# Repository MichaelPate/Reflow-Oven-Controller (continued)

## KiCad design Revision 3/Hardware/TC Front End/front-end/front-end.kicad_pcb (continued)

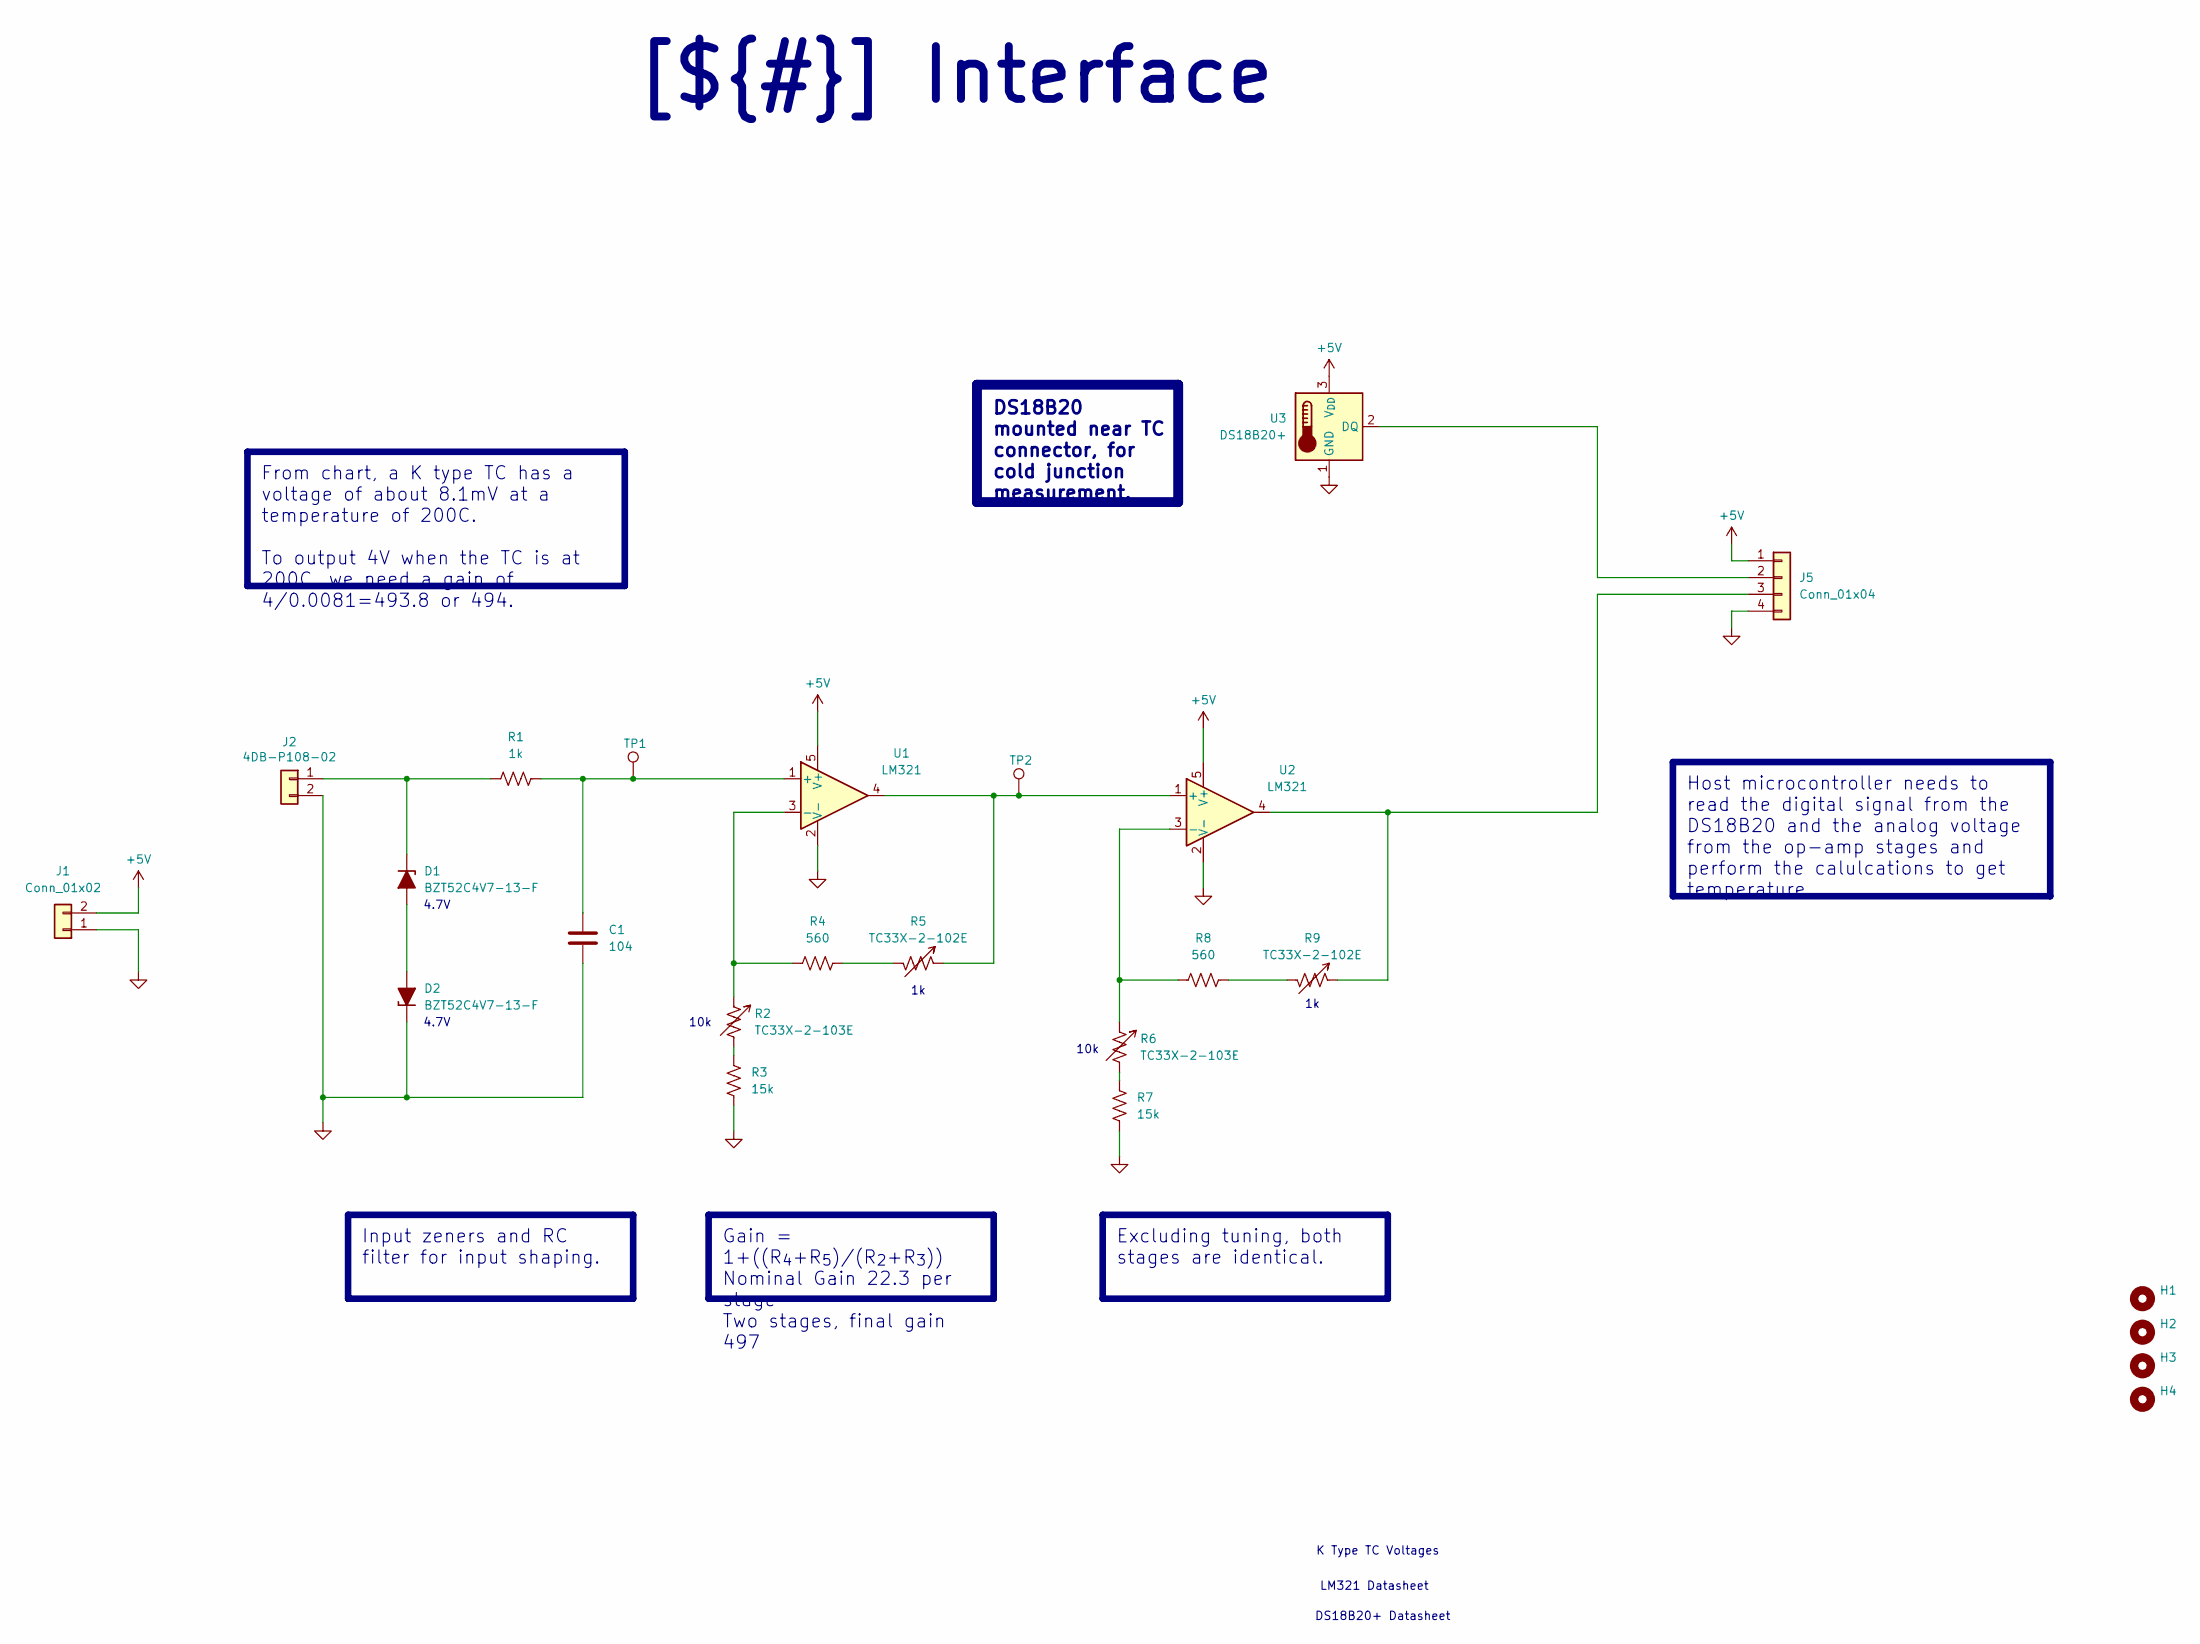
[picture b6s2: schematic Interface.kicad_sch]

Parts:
C1: 104; C_0603_1608Metric_Pad1.08x0.95mm_HandSolder
D1, D2: BZT52C4V7-13-F; D_SOD-123
H1, H2, H3, H4: MountingHole; MountingHole_3.2mm_M3
J1: Conn_01x02; TerminalBlock_Phoenix_MKDS-1,5-2_1x02_P5.00mm_Horizontal
J2: 4DB-P108-02; CONN_4DB-P108-02_TEC
J5: Conn_01x04; PinHeader_1x04_P2.54mm_Vertical
R1: 1k; R_0603_1608Metric_Pad0.98x0.95mm_HandSolder
R2, R6: TC33X-2-103E; Potentiometer_Bourns_TC33X_Vertical
R3, R7: 15k; R_0603_1608Metric_Pad0.98x0.95mm_HandSolder
R4, R8: 560; R_0603_1608Metric_Pad0.98x0.95mm_HandSolder
R5, R9: TC33X-2-102E; Potentiometer_Bourns_TC33X_Vertical
TP1, TP2: TestPoint; TestPoint_THTPad_D2.0mm_Drill1.0mm
U1, U2: LM321; SOT-23-5
U3: DS18B20+; TO-92_Inline

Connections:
+5V: J1.2, J5.1, U1.5 (V+), U2.5 (V+), U3.3 (V_{DD})
GND: C1.2, D2.1 (K), J1.1, J2.2, J5.4, R3.2, R7.2, U1.2 (V-), U2.2 (V-), U3.1 (GND)
unnamed: D1.2 (A), D2.2 (A)
unnamed: D1.1 (K), J2.1, R1.1
unnamed: J5.2, U3.2 (DQ)
unnamed: J5.3, R9.1, U2.4
unnamed: R2.2, R3.1
unnamed: R4.2, R5.2
unnamed: R6.2, R7.1
unnamed: R8.2, R9.2
unnamed: C1.1, R1.2, TP1.1, U1.1 (+)
unnamed: R2.1, R4.1, U1.3 (-)
unnamed: R5.1, TP2.1, U1.4, U2.1 (+)
unnamed: R6.1, R8.1, U2.3 (-)

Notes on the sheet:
4.7V
K Type TC Voltages
10k
LM321 Datasheet
DS18B20+ Datasheet
DS18B20 mounted near TC connector, for cold junction measurement.
Gain = 1+((R_{4}+R_{5})/(R_{2}+R_{3})) Nominal Gain 22.3 per stage Two stages, final gain 497
Input zeners and RC filter for input shaping.
Excluding tuning, both stages are identical.
[${#}] ${TITLE}
Host microcontroller needs to read the digital signal from the DS18B20 and the analog voltage from the op-amp stages and perform the calulcations to get temperature.
From chart, a K type TC has a voltage of about 8.1mV at a temperature of 200C. To output 4V when the TC is at 200C, we need a gain of 4/0.0081=493.8 or 494.

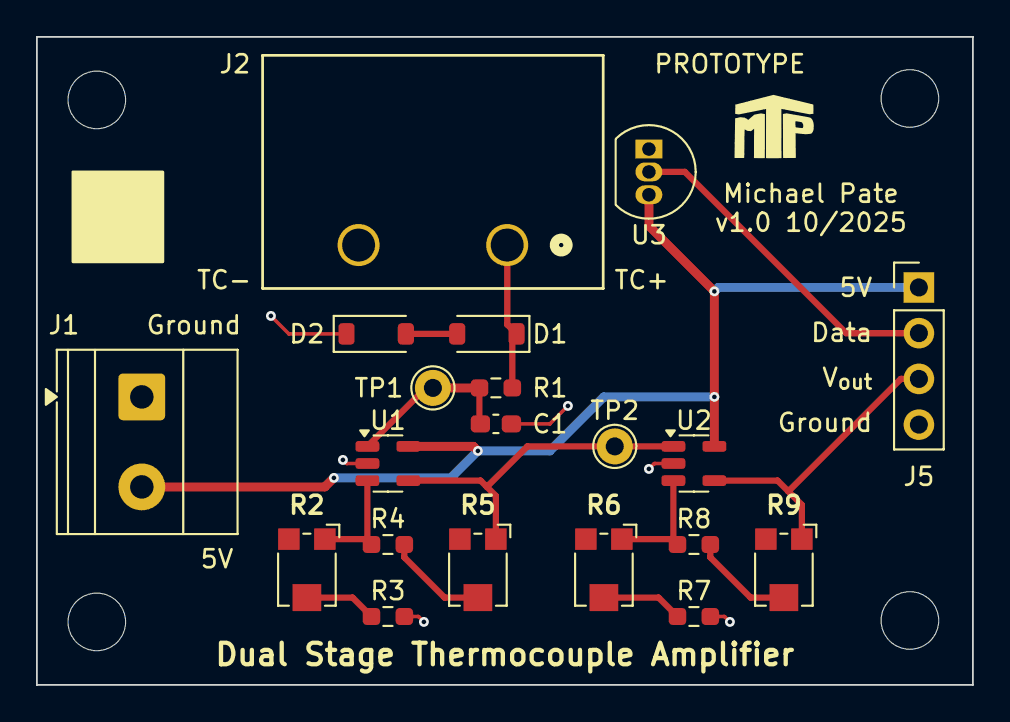
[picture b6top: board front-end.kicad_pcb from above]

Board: 2 copper layers, 52.0 x 36.0 mm, 24 parts (0 on the bottom side), 14 nets.

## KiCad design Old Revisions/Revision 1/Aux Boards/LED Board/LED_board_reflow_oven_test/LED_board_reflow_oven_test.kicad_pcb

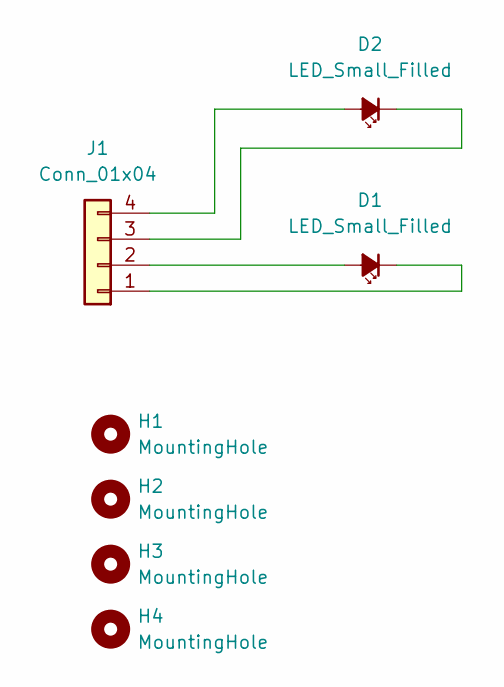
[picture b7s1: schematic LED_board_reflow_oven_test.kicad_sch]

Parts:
D1, D2: LED_Small_Filled; LED_D5.0mm
H1, H2, H3, H4: MountingHole; MountingHole_2.2mm_M2
J1: Conn_01x04; JST_PH_S4B-PH-K_1x04_P2.00mm_Horizontal

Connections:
unnamed: D1.2 (A), J1.2
unnamed: D1.1 (K), J1.1
unnamed: D2.2 (A), J1.4
unnamed: D2.1 (K), J1.3

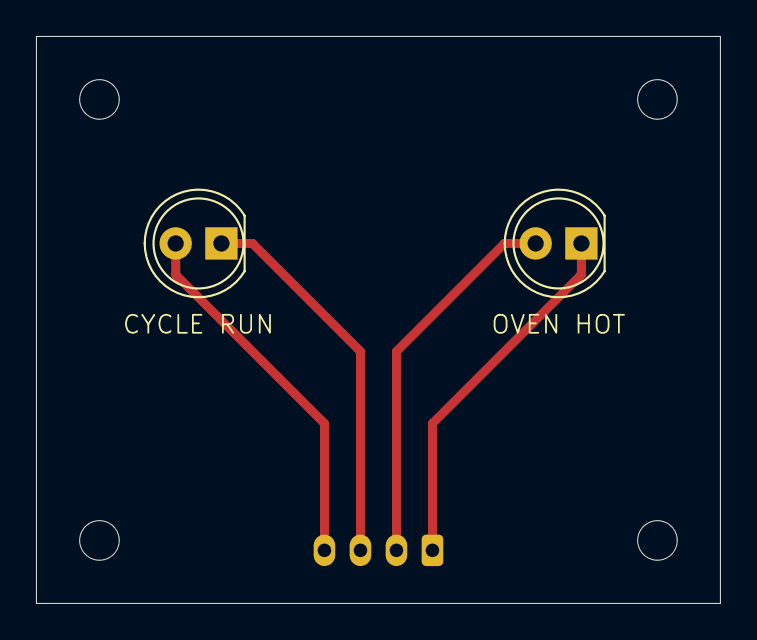
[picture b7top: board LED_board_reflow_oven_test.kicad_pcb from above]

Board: 4 copper layers, 38.0 x 31.5 mm, 7 parts (1 on the bottom side), 4 nets.

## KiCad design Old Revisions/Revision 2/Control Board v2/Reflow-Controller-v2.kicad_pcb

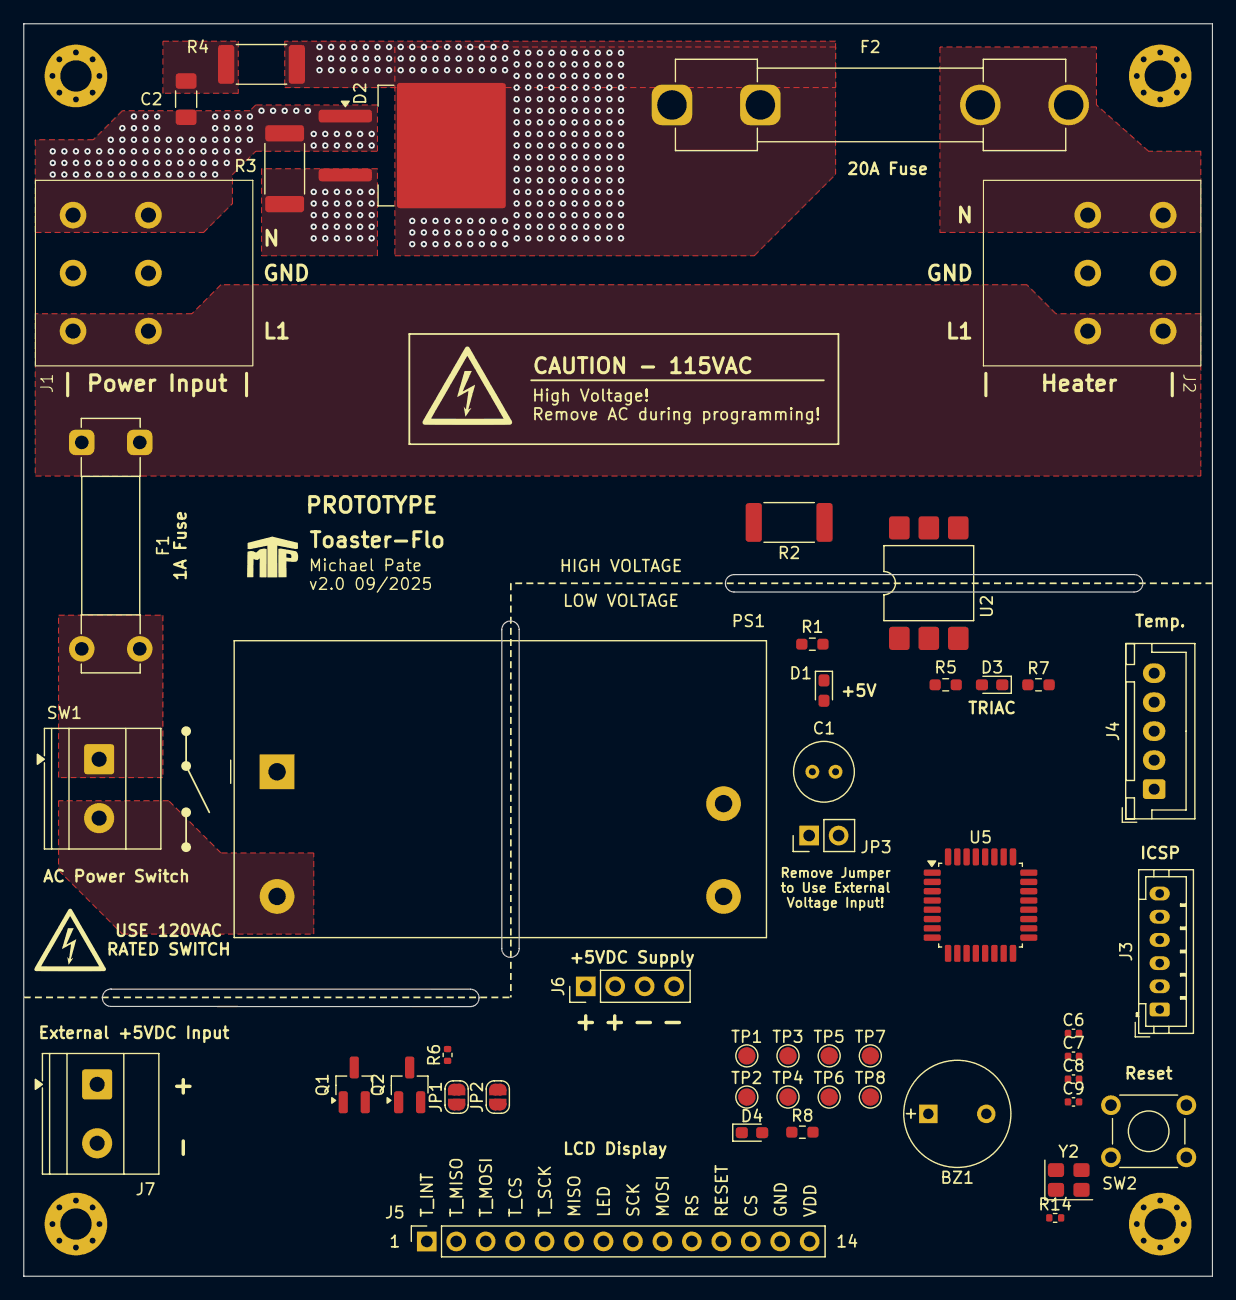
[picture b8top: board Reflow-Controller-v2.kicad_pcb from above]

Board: 4 copper layers, 102.5 x 108.0 mm, 52 parts (0 on the bottom side), 45 nets, no tracks yet.

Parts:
BZ1: CMI-0955-05TH; MagneticBuzzer_PUI_AT-0927-TT-6-R
C1: 100uF; C_Radial_D5.0mm_H5.0mm_P2.00mm
C2: 10nF 250V; C_1206_3216Metric_Pad1.33x1.80mm_HandSolder
C6, C7: 100n; C_0402_1005Metric
C8, C9: 22p; C_0402_1005Metric
D1, D3, D4: RED; LED_0603_1608Metric_Pad1.05x0.95mm_HandSolder
D2: T2035T-8G-RT; TO-263-2
F1: 1A; Fuseholder_Clip-5x20mm_Bel_FC-203-22_Lateral_P17.80x5.00mm_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
F2: 20A; Fuseholder_Clip-6.3x32mm_Littelfuse_122_Inline_P34.21x7.62m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
H1, H2, H3, H4: MountingHole_Pad; MountingHole_2.7mm_M2.5_Pad_Via
J1, J2: 1366005; SPTA-THR 2.53-5.0 P26
J3: ISP; JST_PH_B6B-PH-K_1x06_P2.00mm_Vertical
J4: Conn_01x05; JST_XH_B5B-XH-A_1x05_P2.50mm_Vertical
J5: Conn_01x14; PinSocket_1x14_P2.54mm_Vertical
J6: Conn_01x04; PinHeader_1x04_P2.54mm_Vertical
J7: Conn_01x02; TerminalBlock_Phoenix_MKDS-1,5-2-5.08_1x02_P5.08mm_Horizont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
JP1, JP2: Jumper_2_Open; SolderJumper-2_P1.3mm_Open_RoundedPad1.0x1.5mm
JP3: Jumper_2_Open; PinHeader_1x02_P2.54mm_Vertical
PS1: IRM-10-5; Converter_ACDC_MeanWell_IRM-10-xx_THT
Q1: SQ2315CES-T1_GE3; SOT-23_Handsoldering
Q2: BSS127 H6327; SOT-23_Handsoldering
R1, R5, R7, R8: 330; R_0603_1608Metric_Pad0.98x0.95mm_HandSolder
R2, R3: 330; R_2512_6332Metric_Pad1.40x3.35mm_HandSolder
R4: 39; R_2512_6332Metric_Pad1.40x3.35mm_HandSolder
R6: 330; R_0402_1005Metric
R14: 10k; R_0402_1005Metric
SW1: SW_SPST; TerminalBlock_Phoenix_MKDS-1,5-2-5.08_1x02_P5.08mm_Horizont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
SW2: SW_Push; SW_TH_Tactile_Omron_B3F-102x
TP1, TP2, TP3, TP4, TP5, TP6, TP7, TP8: TestPoint; TestPoint_Pad_D1.5mm
U2: MOC3083S-TA1; SMDIP-6_W9.53mm
U5: ATmega328PB-A; TQFP-32_7x7mm_P0.8mm
Y2: 16MHz; Crystal_SMD_3225-4Pin_3.2x2.5mm

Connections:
/Project Architecture/AC-DC Power Supply/D1_K: D1.1 (K), R1.1
/Project Architecture/AC-DC Power Supply/L1_F1: F1.2, SW1.1 (A)
/Project Architecture/AC-DC Power Supply/L1_F1_SW: PS1.2 (AC/L), SW1.2 (B)
/Project Architecture/AC-DC Power Supply/VDD_AC_DC: JP3.1 (A), PS1.4 (+Vo)
/Project Architecture/Heater Control/D3_K: D3.1 (K), R7.1
/Project Architecture/Heater Control/D_R5_OPTO: R5.2, U2.1
/Project Architecture/Heater Control/L1_F2: D2.2 (A2), F2.1, R2.2, R4.2
/Project Architecture/Heater Control/L1_F2_OPTO: R2.1, U2.6
/Project Architecture/Heater Control/L1_F2_RC: C2.1, R4.1
/Project Architecture/Heater Control/L1_HEATER: F2.2, J2.3
/Project Architecture/Heater Control/LN_OPTO: D2.3 (G), R3.2, U2.4
/Project Architecture/Interface/VDD_BL: J5.7, JP1.2 (B)
/Project Architecture/Interface/VDD_BL_FET: JP1.1 (A), Q1.3 (S)
/Project Architecture/Interface/VDD_BL_SUP: JP2.1 (A), Q1.1 (D)
/Project Architecture/Interface/VDD_BUZZ: BZ1.1 (+), R6.1
/Project Architecture/Interface/VSS_BUZZ: BZ1.2 (-), Q2.1 (D)
/Project Architecture/Microcontroller/D4_K: D4.1 (K), R8.1
/Project Architecture/Microcontroller/DB_6: TP7.1, U5.10 (PD6)
/Project Architecture/Microcontroller/DB_7: D4.2 (A), TP8.1, U5.11 (PD7)
/Project Architecture/Microcontroller/DB_8: TP1.1, U5.12 (PB0)
/Project Architecture/Microcontroller/DB_A3: TP2.1, U5.26 (PC3)
/Project Architecture/Microcontroller/DB_A4: TP3.1, U5.27 (PC4)
/Project Architecture/Microcontroller/DB_A5: TP4.1, U5.28 (PC5)
/Project Architecture/Microcontroller/DB_AVR_RX: TP5.1, U5.30 (PD0)
/Project Architecture/Microcontroller/DB_AVR_TX: TP6.1, U5.31 (PD1)
/Project Architecture/Microcontroller/XTAL_1: C8.2, U5.7 (XTAL1/PB6), Y2.2
/Project Architecture/Microcontroller/XTAL_2: C9.2, U5.8 (XTAL2/PB7), Y2.1
D_Buzzer: Q2.2 (G), U5.14 (PB2)
D_Heater: D3.2 (A), R5.1, U5.13 (PB1)
D_TC_Select: J4.4, U5.23 (PC0)
D_TFT_Backlight: Q1.2 (G), U5.1 (PD3)
D_TFT_Register: J5.10, U5.9 (PD5)
D_TFT_Reset: J5.11, U5.2 (PD4)
D_TFT_Select: J5.12, U5.25 (PC2)
D_Touch_IRQ: J5.1, U5.32 (PD2)
D_Touch_Select: J5.4, U5.24 (PC1)
GND: C1.2, C6.1, C7.1, C8.1, C9.1, J3.6, J4.1, J5.13, J6.3, J6.4, J7.2, PS1.3 (-Vo), Q2.3 (S), R1.2, R7.2, R8.2, SW2.1, U2.2, U5.5 (GND), U5.21 (GND)
GNDPWR: H1.1, H2.1, H3.1, H4.1, J1.2, J2.2
ICSP_MISO: J3.4, J4.5, J5.2, J5.6, U5.16 (PB4)
ICSP_MOSI: J3.3, J5.3, J5.9, U5.15 (PB3)
ICSP_RST: J3.2, R14.1, SW2.2, U5.29 (~RESET/PC6)
ICSP_SCK: J3.5, J4.3, J5.5, J5.8, U5.17 (PB5)
L1: F1.1, J1.3, J2.1
LN: C2.2, D2.1 (A1), J1.1, PS1.1 (AC/N), R3.1
VDD: C1.1, C6.2, C7.2, D1.2 (A), J3.1, J4.2, J5.14, J6.1, J6.2, J7.1, JP2.2 (B), JP3.2 (B), R6.2, R14.2, U5.4 (VCC), U5.18 (AVCC)

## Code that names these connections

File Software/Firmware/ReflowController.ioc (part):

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Mcu.Name=STM32F401R(D-E)Tx
Mcu.Package=LQFP64
Mcu.UserName=STM32F401RETx
PA0-WKUP.GPIOParameters=GPIO_Label
PA0-WKUP.GPIO_Label=C0_Output
PA0-WKUP.Signal=GPIO_Output
PA1.GPIOParameters=GPIO_Label
PA1.GPIO_Label=C1_Output
PA1.Signal=GPIO_Output
PA2.GPIOParameters=GPIO_Label
PA2.GPIO_Label=TC_Vout
PA2.Signal=ADCx_IN2
PA4.GPIOParameters=GPIO_Label
PA4.GPIO_Label=C2_Output
PA4.Signal=GPIO_Output
PA5.GPIOParameters=GPIO_Label
PA5.GPIO_Label=LED_BUILTIN
PA5.Signal=GPIO_Output
PA8.GPIOParameters=PinState,GPIO_PuPd,GPIO_Label
PA8.GPIO_Label=MAX6675_CS
PA8.GPIO_PuPd=GPIO_NOPULL
PA8.PinState=GPIO_PIN_SET
PA8.Signal=GPIO_Output
PA9.GPIOParameters=GPIO_Label
PA9.GPIO_Label=HEAT_OUT
PA9.Signal=GPIO_Output
PB10.GPIOParameters=GPIO_Label
PB10.GPIO_Label=MAX6675_CLK
PB10.Mode=RX_Only_Simplex_Unidirect_Master
PB10.Signal=SPI2_SCK
PB12.GPIOParameters=GPIO_Label
PB12.GPIO_Label=TRIAC_JCT_TEMP
PB12.Signal=GPIO_Input
PB13.GPIOParameters=GPIO_Label
PB13.GPIO_Label=CJ_TEMP
PB13.Signal=GPIO_Input
PB14.GPIOParameters=GPIO_Label
PB14.GPIO_Label=FAN1
PB14.Signal=GPIO_Output
PB15.GPIOParameters=GPIO_Label
PB15.GPIO_Label=FAN2
PB15.Signal=GPIO_Output
PB3.GPIOParameters=GPIO_PuPd,GPIO_Label
PB3.GPIO_Label=R0_Input
PB3.GPIO_PuPd=GPIO_PULLDOWN
PB3.Signal=GPIO_Input
PB4.GPIOParameters=GPIO_PuPd,GPIO_Label
PB4.GPIO_Label=R1_Input
PB4.GPIO_PuPd=GPIO_PULLDOWN
PB4.Signal=GPIO_Input
PB5.GPIOParameters=GPIO_PuPd,GPIO_Label
PB5.GPIO_Label=R2_Input
PB5.GPIO_PuPd=GPIO_PULLDOWN
PB5.Signal=GPIO_Input
PB6.GPIOParameters=GPIO_PuPd,GPIO_Label
PB6.GPIO_Label=R3_Input
PB6.GPIO_PuPd=GPIO_PULLDOWN
PB6.Signal=GPIO_Input
PB8.Mode=I2C
PB8.Signal=I2C1_SCL
PB9.Mode=I2C
PB9.Signal=I2C1_SDA
PC13-ANTI_TAMP.GPIOParameters=GPIO_Label
PC13-ANTI_TAMP.GPIO_Label=Button
PC13-ANTI_TAMP.Signal=GPIO_Input
PC2.GPIOParameters=GPIO_Label
PC2.GPIO_Label=MAX6675_SO
PC2.Mode=RX_Only_Simplex_Unidirect_Master
PC2.Signal=SPI2_MISO
PC7.GPIOParameters=GPIO_Label
PC7.GPIO_Label=Buzzer
PC7.Signal=GPIO_Output
RCC.HSE_VALUE=25000000
RCC.SYSCLKFreq_VALUE=16000000
board=custom

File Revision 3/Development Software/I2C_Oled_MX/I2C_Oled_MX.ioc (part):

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Mcu.Name=STM32F401R(D-E)Tx
Mcu.Package=LQFP64
Mcu.UserName=STM32F401RETx
PA13.GPIOParameters=GPIO_Label
PA13.GPIO_Label=TMS
PA13.Mode=Trace_Asynchronous_SW
PA13.Signal=SYS_JTMS-SWDIO
PA14.GPIOParameters=GPIO_Label
PA14.GPIO_Label=TCK
PA14.Mode=Trace_Asynchronous_SW
PA14.Signal=SYS_JTCK-SWCLK
PA2.GPIOParameters=GPIO_Speed,GPIO_PuPd,GPIO_Label,GPIO_Mode
PA2.GPIO_Label=USART_TX
PA2.GPIO_Mode=GPIO_MODE_AF_PP
PA2.GPIO_PuPd=GPIO_NOPULL
PA2.GPIO_Speed=GPIO_SPEED_FREQ_LOW
PA2.Mode=Asynchronous
PA2.Signal=USART2_TX
PA3.GPIOParameters=GPIO_Speed,GPIO_PuPd,GPIO_Label,GPIO_Mode
PA3.GPIO_Label=USART_RX
PA3.GPIO_Mode=GPIO_MODE_AF_PP
PA3.GPIO_PuPd=GPIO_NOPULL
PA3.GPIO_Speed=GPIO_SPEED_FREQ_LOW
PA3.Mode=Asynchronous
PA3.Signal=USART2_RX
PA5.GPIOParameters=GPIO_Speed,GPIO_PuPd,GPIO_Label,GPIO_Mode
PA5.GPIO_Label=LD2 [Green Led]
PA5.GPIO_Mode=GPIO_MODE_OUTPUT_PP
PA5.GPIO_PuPd=GPIO_NOPULL
PA5.GPIO_Speed=GPIO_SPEED_FREQ_LOW
PA5.Signal=GPIO_Output
PB3.GPIOParameters=GPIO_Label
PB3.GPIO_Label=SWO
PB3.Mode=Trace_Asynchronous_SW
PB3.Signal=SYS_JTDO-SWO
PB8.Mode=I2C
PB8.Signal=I2C1_SCL
PB9.Mode=I2C
PB9.Signal=I2C1_SDA
PC13-ANTI_TAMP.GPIOParameters=GPIO_PuPd,GPIO_Label,GPIO_ModeDefaultEXTI
PC13-ANTI_TAMP.GPIO_Label=B1 [Blue PushButton]
PC13-ANTI_TAMP.GPIO_ModeDefaultEXTI=GPIO_MODE_IT_FALLING
PC13-ANTI_TAMP.GPIO_PuPd=GPIO_NOPULL
PC13-ANTI_TAMP.Signal=GPXTI13
PC14-OSC32_IN.Mode=LSE-External-Oscillator
PC14-OSC32_IN.Signal=RCC_OSC32_IN
PC15-OSC32_OUT.Mode=LSE-External-Oscillator
PC15-OSC32_OUT.Signal=RCC_OSC32_OUT
PH0\ -\ OSC_IN.Mode=HSE-External-Clock-Source
PH0\ -\ OSC_IN.Signal=RCC_OSC_IN
PH1\ -\ OSC_OUT.Mode=HSE-External-Clock-Source
PH1\ -\ OSC_OUT.Signal=RCC_OSC_OUT
RCC.HSE_VALUE=8000000
RCC.SYSCLKFreq_VALUE=84000000
RCC.SYSCLKSource=RCC_SYSCLKSOURCE_PLLCLK
board=NUCLEO-F401RE
boardIOC=true

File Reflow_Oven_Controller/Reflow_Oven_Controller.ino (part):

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// LCD Hardware, Nokia 5110 48x84
#define LCD_CLK 7
#define LCD_DIN 6
#define LCD_DC 5
#define LCD_CS 4
#define LCD_RST 3
// Buttons for selecting profiles and start/stop
#define BTN1 A0
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#define TOP_ELEMENT 9   // An LED for prototyping, an LED and relay coil in production
#define BOT_ELEMENT 10  // Same for this one
// Thermocouple SPI interface
#define TC_CS 11
#define TC_DAT 12
#define TC_CLK 8
// For indicating cycle complete
#define BUZZER 2


// Instantiate all objects ////////////////////////////////////////////////////////////////////////////////////////////////////////////
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  lcd.setContrast(60);
  
  // put your setup code here, to run once:
  pinMode(BUZZER, OUTPUT);
  pinMode(TOP_ELEMENT, OUTPUT);
  pinMode(BOT_ELEMENT, OUTPUT);
  pinMode(HEAT_PILOT, OUTPUT);
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
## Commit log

2025-08-24 Add revision 1 files
2025-08-24 add new rev2 project
2025-08-24 initial layout
2025-08-25 add rev1 files for changing into rev2
2025-08-28 Switch v2 design to template
2025-08-29 Finish preparing the template for v2 design
2025-08-29 Draft power supply and TRIAC driver circuits
2025-08-29 add resource links
2025-08-29 draft microcontroller and interface circuits, still need to finish interfaces
2025-09-08 work on PCB layout
2025-09-08 Move notes on schematic
2025-09-08 add silkscreen to bottom of board
2025-09-08 change to glass fuses instead of blade fuses
2025-09-09 got most HV routed
2025-09-09 add external 5v input and move stuff around on board
2025-09-09 change silkscreen
2025-09-09 add initial project for power board
2025-09-09 Import schematics from single-board design
2025-09-10 schematic mostly done, start board layout
2025-09-12 add isolation to pcb design
2025-09-14 pcb design
2025-09-20 PCB layout is generally complete
2025-09-20 generate production files
2025-09-20 Revise project structure
2025-09-24 Fix 3D Models, readjust traces on power board
2025-09-26 work on power board layout
2025-10-18 generate gerbers for power board fab
2025-10-18 complete schematic for power board
2025-10-18 New project for temperature front end
2025-10-18 save project template to new version
2025-10-18 Project template fully initialized
2025-10-18 fix typo in page numbers
2025-10-18 Analog schematic substantially complete
2025-10-18 Add some notes to the schematic
2025-10-18 Add references
2025-10-18 Fix typo in notes on gain
2025-10-18 Add footprints to schematic
2025-10-18 Add parts to PCB and get models. Layout can now begin
2025-10-18 Rename files
2025-10-18 PCB layout complete, ready for routing
2025-10-18 PCB routing complete, ready for production
2025-10-18 Add test points for inter stages
2025-10-18 Sent PCB to production, add images to schematic
2025-10-18 power and analog boards sent to production
2025-10-18 Template set up
2025-10-18 Add keypad to schematic
2025-10-19 board complete and fab files generated, sent to fab
2025-10-19 regenerated fab files and sent to fab
2025-10-24 Change AC-DC supply fuse holder part number, ordered the wrong one
2025-10-27 Arduino demo for OLED is working
2026-01-16 STM32 OLED Demo
2026-01-18 Blinking LED is working
2026-01-18 STM32 OLED with HAL is working. Add 5x7 font for text
2026-01-25 Add all work up to now
2026-01-25 Rearrange files
2026-01-25 Add new empty project based off keypad oled state machine IOC
2026-01-25 Change SPI parameters for thermocouple, generate code, and rebuild project
2026-01-25 Add OLED source code, fonts, methods. OLED is working with simple Hello World text
2026-01-25 TC is working and displaying on the OLED
2026-01-25 Rough PID loop implemented, needs tuned. Keypad still does not do anything yet
2026-01-31 Add image to README
2026-01-31 add new project for keypad board
2026-02-01 PCB design complete, ready for fitment testing
2026-02-01 move start stop keys half a mm and then made fabrication outputs, fitment check good, ready for production
2026-02-01 almost forgot traces, route board and send to production
2026-02-01 edit silkscreen
2026-02-01 Add daughter board for power and reset, send to production
2026-02-04 schematic capture should be complete pending a review
2026-02-04 edit schematic to pass schematic DRC
2026-02-04 add details, need to change TC amp gain for different voltage and temperature
2026-02-04 add heatsink mounting holes, change a few footprints, clean up schematic
2026-02-04 add capacitance to 5v power supply
2026-02-04 plot pdf schematic preliminary 0
2026-02-06 working on PCB layout
2026-02-16 routing halfway done, trying autorouter to finish low voltage signals
2026-03-01 Finish board layout
2026-03-01 Generate fabrication documents
